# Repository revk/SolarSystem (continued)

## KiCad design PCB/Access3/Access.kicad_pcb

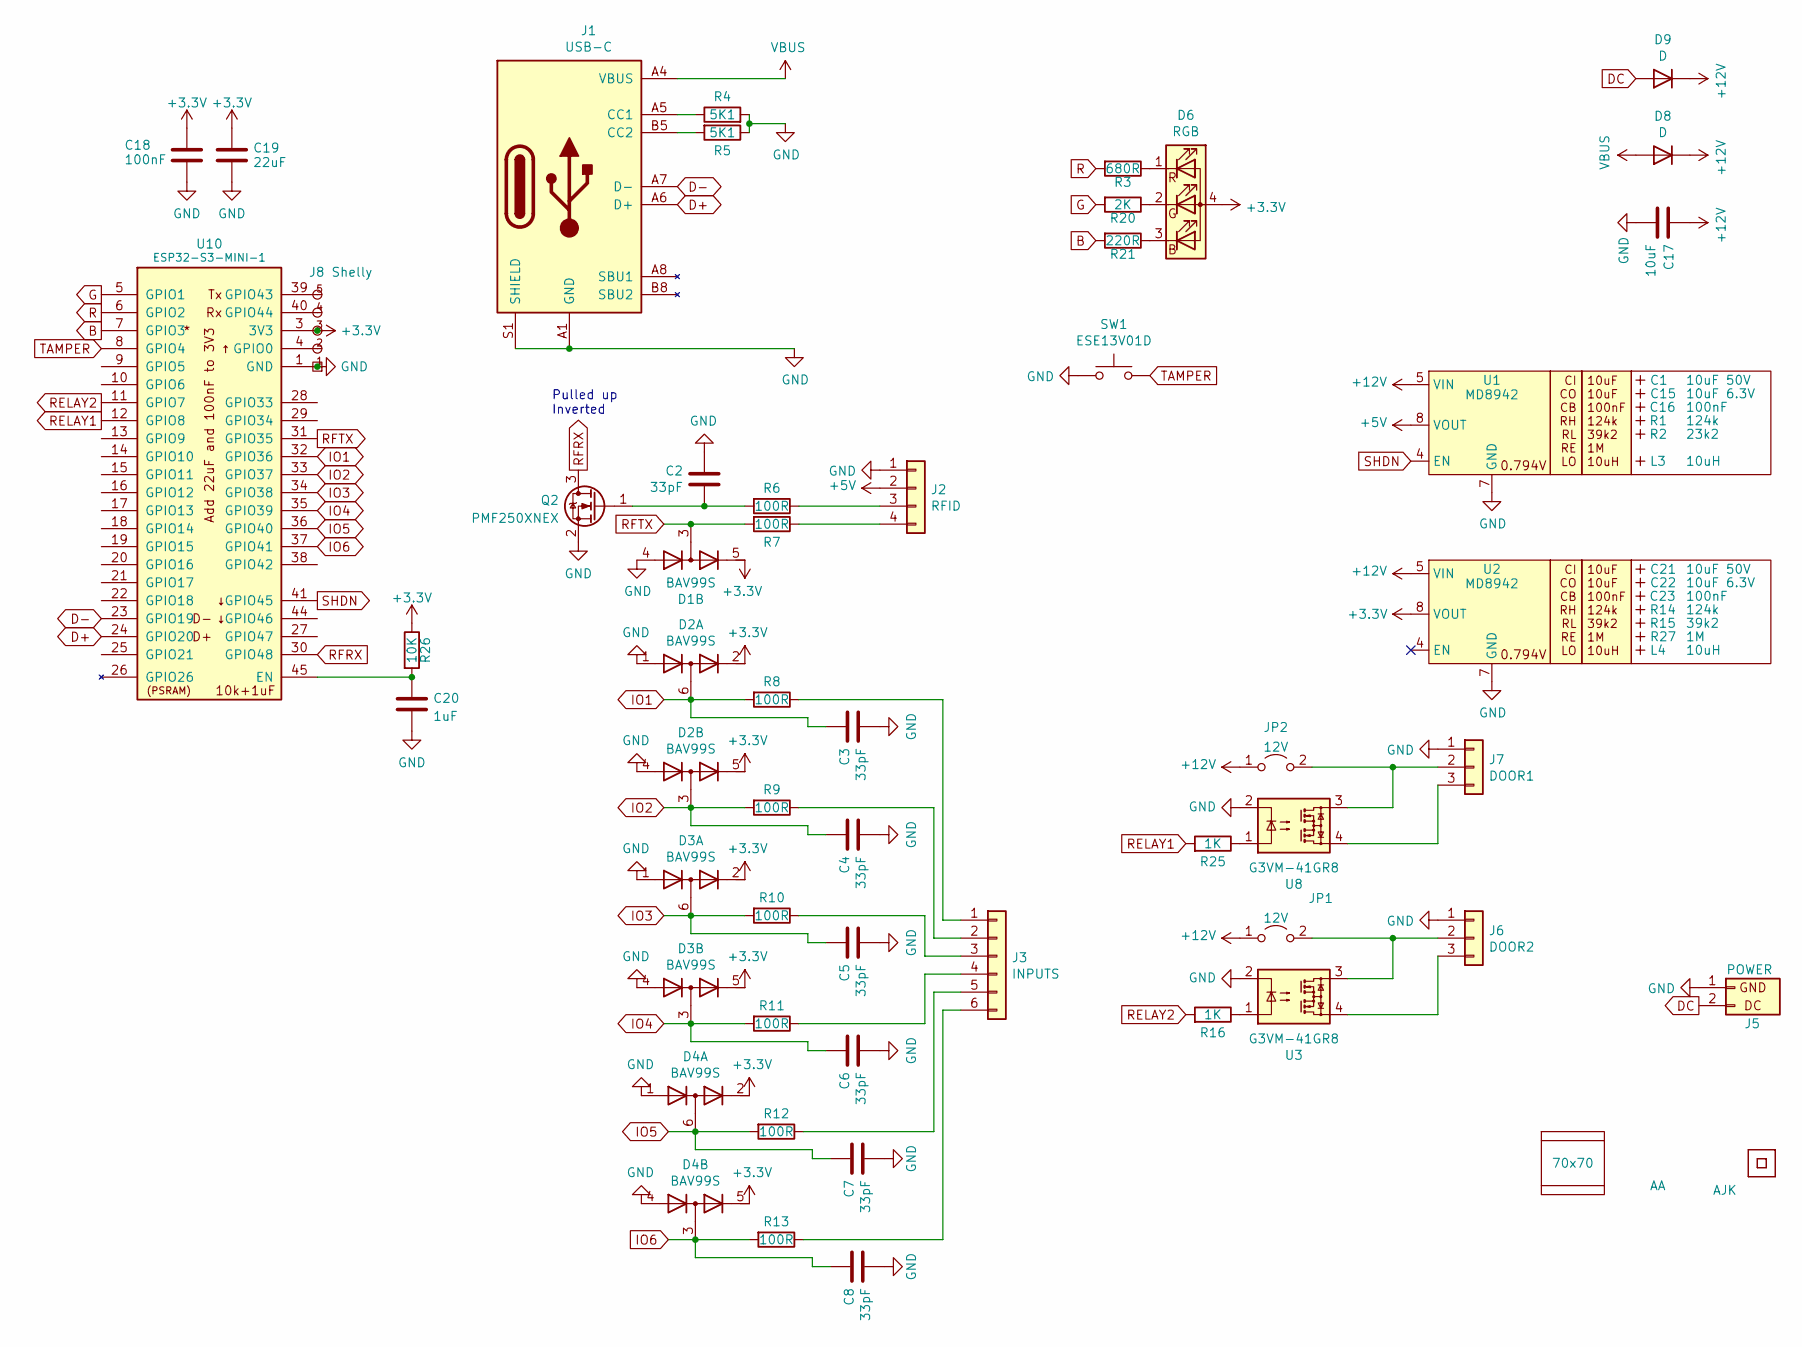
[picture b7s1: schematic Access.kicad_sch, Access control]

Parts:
C1, C21: 10uF 50V; C_0603_; LCSC Part # C1591
C2, C3, C4, C5, C6, C7, C8: 33pF; C_0402
C15, C22: 10uF 6.3V; C_0603_; LCSC Part # C1691
C16, C23: 100nF; C_0603_
C17: 10uF; C_0402
C18: 100nF; C_0402
C19: 22uF; C_0402
C20: 1uF; C_0402
D1, D2, D3, D4: BAV99S; SOT-363_SC-70-6; JLCPCB Rotation Offset 90
D6: RGB; LED-RGB-1.6x1.6; Part No APTF1616LSEEZGKQBKC; LCSC Part # C264508
D8, D9: D; D_1206; LCSC Part # C143805
J1: USB-C; USC16-TR; LCSC Part # C709357
J2: RFID; PTSM-HH-4-RA
J3: INPUTS; PTSM-HH-6-RA
J5: POWER; PTSM-HH1-2-RA
J6: DOOR2; PTSM-HH1-3-RA-W
J7: DOOR1; PTSM-HH1-3-RA
J8: Shelly
JP1, JP2: 12V; SolderJumper-2_P1.3mm_Open_RoundedPad1.0x1.5mm
L3, L4: 10uH; L_4x4_
Logo1: AJK
PCB1: 70x70; PCB7070
Q2: PMF250XNEX; SOT-323_SC-70; Part No PMF250XNEX; LCSC Part # C504047
R1, R14: 124k; R_0402_
R2: 23k2; R_0402_
R3: 680R; R_0402
R4, R5: 5K1; R_0402
R6, R7, R8, R9, R10, R11, R12, R13: 100R; R_0402
R15: 39k2; R_0402_
R16, R25: 1K; R_0402
R20: 2K; R_0402
R21: 220R; R_0402
R26: 10K; R_0402
R27: 1M; R_0402_
SW1: ESE13V01D; ESE13
U1, U2: MD8942; SOT-23-6-MD8942; LCSC Part # C2684786
U3, U8: G3VM-41GR8; Special-SOP-4-3.7x4.55; LCSC Part # C2691601
U7: QR; QR-SS
U9: AA
U10: ESP32-S3-MINI-1; LCSC Part # C3013941
V1, V2: VCUT70

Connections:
+3.3V: C18.1, C19.1, D1.5 (K4), D2.2 (K2), D2.5 (K4), D3.2 (K2), D3.5 (K4), D4.2 (K2), D4.5 (K4), D6.4 (A), J8.3 (3V3), R26.1, U2.8 (VOUT), U10.3 (3V3)
+5V: J2.2, U1.8 (VOUT)
+12V: C17.1, D8.1 (K), D9.1 (K), JP1.1 (A), JP2.1 (A), U1.5 (VIN), U2.5 (VIN)
B: R21.2, U10.7 (GPIO3)
D+: J1.A6 (D+), J1.B6 (D+), U10.24 (GPIO20)
D-: J1.A7 (D-), J1.B7 (D-), U10.23 (GPIO19)
DC: D9.2 (A), J5.2 (DC)
G: R20.2, U10.5 (GPIO1)
GND: C2.1, C3.2, C4.2, C5.2, C6.2, C7.2, C8.2, C17.2, C18.2, C19.2, C20.2, D1.4 (A3), D2.1 (A1), D2.4 (A3), D3.1 (A1), D3.4 (A3), D4.1 (A1), D4.4 (A3), J1.A1 (GND), J1.A12 (GND), J1.B1 (GND), J1.B12 (GND), J1.S1 (SHIELD), J2.1, J5.1 (GND), J6.1, J7.1, J8.1 (GND), Q2.2 (S), R4.2, R5.1, SW1.1, U1.2 (GND), U1.7 (GND), U2.2 (GND), U2.7 (GND), U3.2, U8.2, U10.1 (GND), U10.2 (GND), U10.42 (GND), U10.43 (GND), U10.46 (GND), U10.47 (GND), U10.48 (GND), U10.49 (GND), U10.50 (GND), U10.51 (GND), U10.52 (GND), U10.53 (GND), U10.54 (GND), U10.55 (GND), U10.56 (GND), U10.57 (GND), U10.58 (GND), U10.59 (GND), U10.60 (GND), U10.61 (GND), U10.62 (GND), U10.63 (GND), U10.64 (GND), U10.65 (GND)
IO1: C3.1, D2.6 (K3A4), R8.2, U10.32 (GPIO36)
IO2: C4.1, D2.3 (K1A2), R9.2, U10.33 (GPIO37)
IO3: C5.1, D3.6 (K3A4), R10.2, U10.34 (GPIO38)
IO4: C6.1, D3.3 (K1A2), R11.2, U10.35 (GPIO39)
IO5: C7.1, D4.6 (K3A4), R12.2, U10.36 (GPIO40)
IO6: C8.1, D4.3 (K1A2), R13.2, U10.37 (GPIO41)
unnamed: D6.3 (BK), R21.1
unnamed: D6.2 (GK), R20.1
unnamed: D6.1 (RK), R3.1
unnamed: J1.A5 (CC1), R4.1
unnamed: J1.B5 (CC2), R5.2
unnamed: J2.3, R6.1
unnamed: J2.4, R7.1
unnamed: J3.1, R8.1
unnamed: J3.2, R9.1
unnamed: J3.3, R10.1
unnamed: J3.4, R11.1
unnamed: J3.5, R12.1
unnamed: J3.6, R13.1
unnamed: J6.2, JP1.2 (B), U3.3
unnamed: J6.3, U3.4
unnamed: J7.2, JP2.2 (B), U8.3
unnamed: J7.3, U8.4
unnamed: J8.2 (0), U10.4 (GPIO0)
unnamed: J8.4 (Rx), U10.40 (GPIO44)
unnamed: J8.5 (Tx), U10.39 (GPIO43)
unnamed: C2.2, Q2.1 (G), R6.2
unnamed: R16.1, U3.1
unnamed: R25.1, U8.1
unnamed: C20.1, R26.2, U10.45 (EN)
R: R3.2, U10.6 (GPIO2)
RELAY1: R25.2, U10.12 (GPIO8)
RELAY2: R16.2, U10.11 (GPIO7)
RFRX: Q2.3 (D), U10.30 (GPIO48)
RFTX: D1.3 (K1A2), R7.2, U10.31 (GPIO35)
SHDN: U1.4 (EN), U10.41 (GPIO45)
TAMPER: SW1.2, U10.8 (GPIO4)
VBUS: D8.2 (A), J1.A4 (VBUS), J1.A9 (VBUS), J1.B4 (VBUS), J1.B9 (VBUS)

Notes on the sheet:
Pulled up Inverted

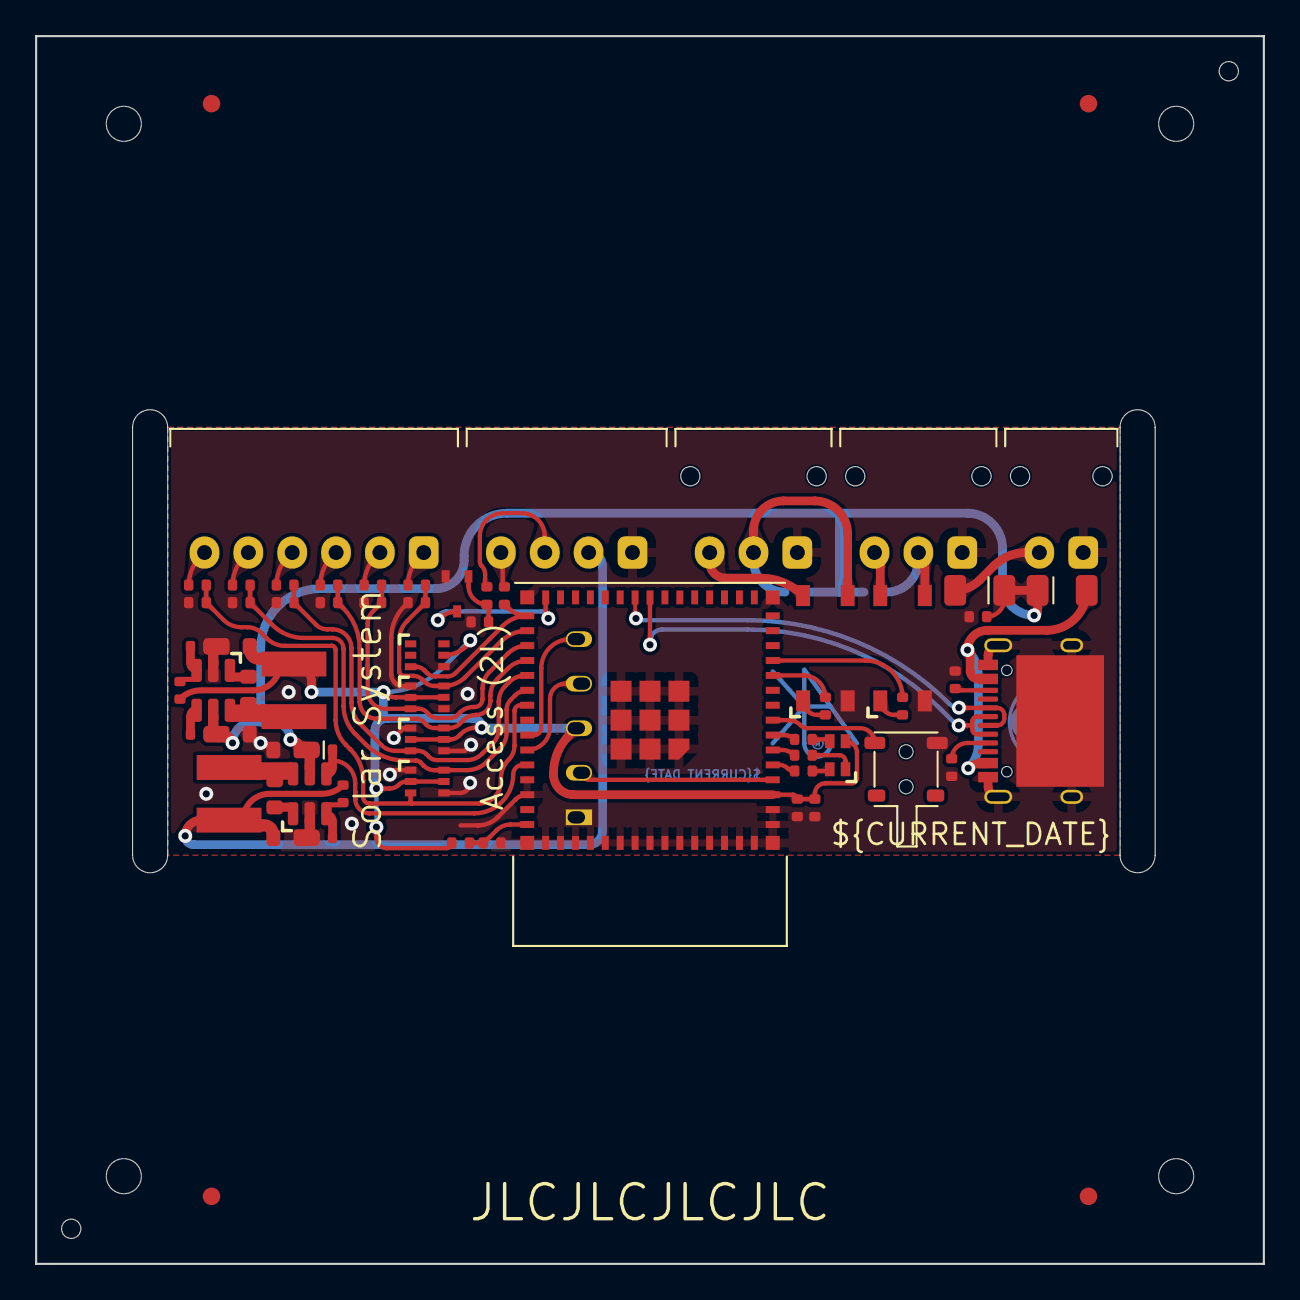
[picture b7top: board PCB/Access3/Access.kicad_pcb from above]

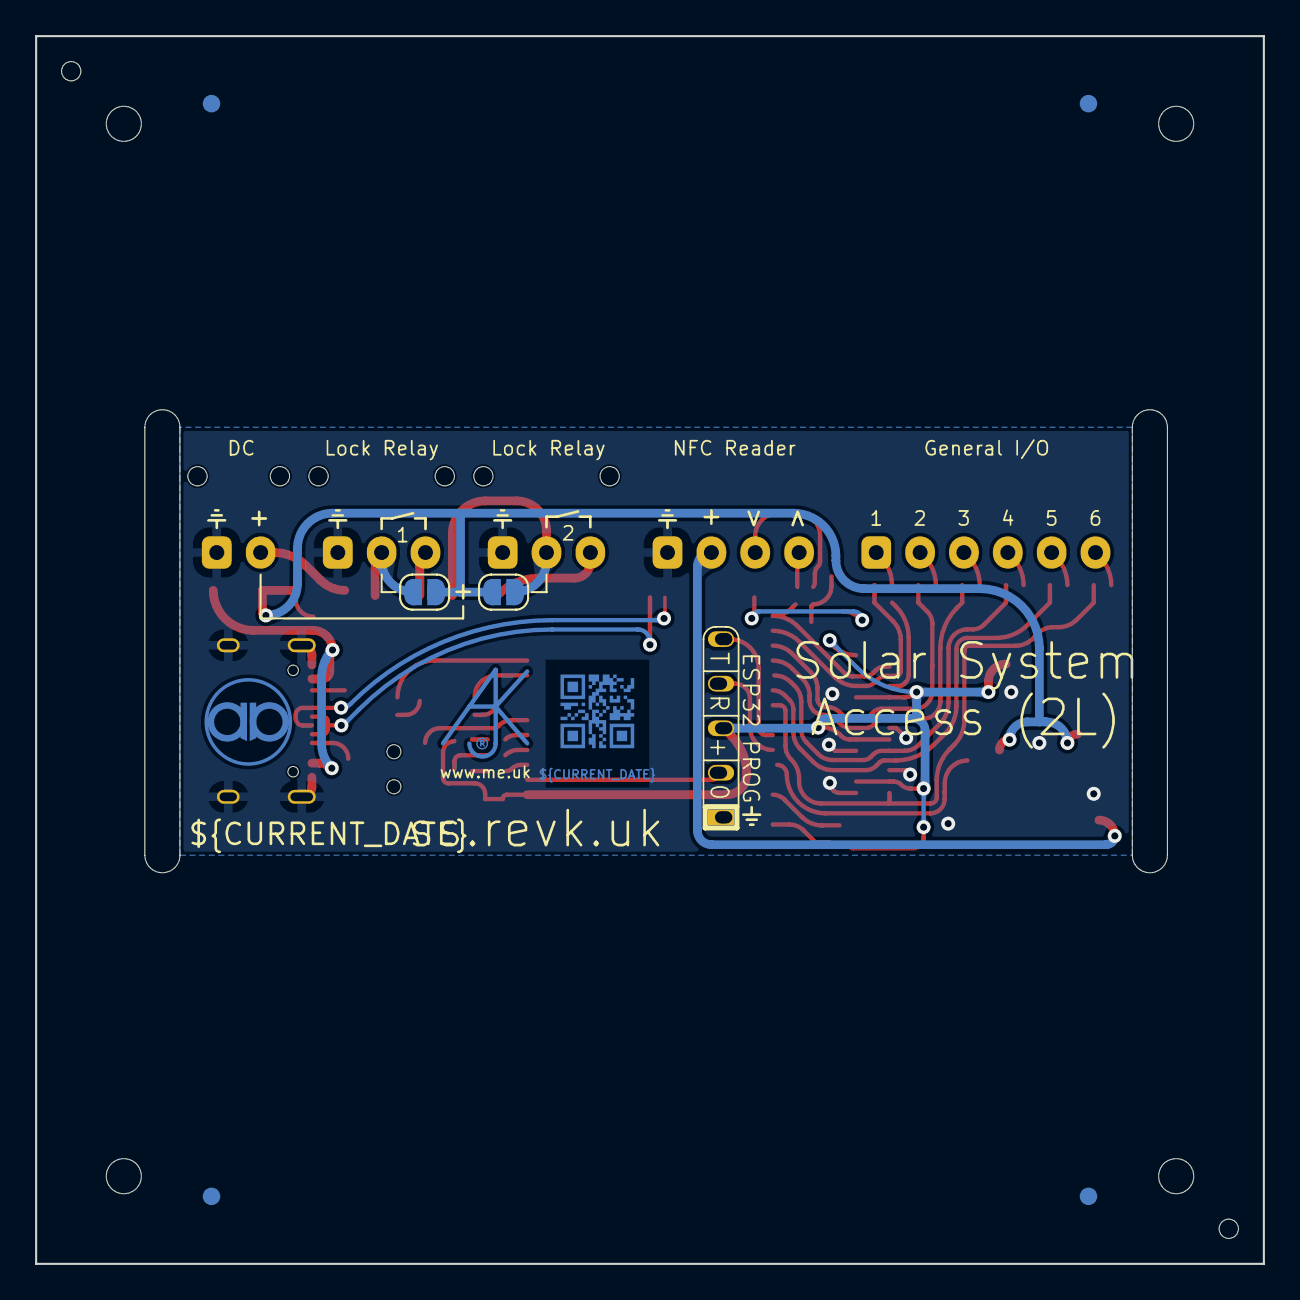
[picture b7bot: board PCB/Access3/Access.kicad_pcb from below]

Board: 2 copper layers, 70.0 x 70.0 mm, 69 parts (6 on the bottom side), 47 nets.

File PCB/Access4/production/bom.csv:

Designator,Footprint,Quantity,Value,LCSC Part #
"C1, C21",C_0603_,2,10uF 50V,C1591
"C15, C22",C_0603_,2,10uF 6.3V,C1691
"C16, C23",C_0603_,2,100nF,
C17,C_0402,1,10uF,
C18,C_0402,1,100nF,
C19,C_0402,1,22uF,
"C2, C3, C4, C5, C6, C7, C8",C_0402,7,33pF,
C20,C_0402,1,1uF,
"D1, D2, D3, D4",SOT-363_SC-70-6,4,BAV99S,
D6,LED-RGB-1.6x1.6,1,RGB,C264508
"D8, D9",D_1206,2,D,C143805
J1,USC16-TR,1,USB-C,C709357
J2,PTSM-HH-4-RA,1,RFID,
J3,PTSM-HH-6-RA,1,INPUTS,
J5,PTSM-HH1-2-RA,1,POWER,
J6,PTSM-HH1-3-RA-W,1,DOOR2,
J7,PTSM-HH1-3-RA,1,DOOR1,
"L3, L4",L_4x4_,2,10uH,
Q2,SOT-323_SC-70,1,PMF250XNEX,C504047
"R1, R14",R_0402_,2,124k,
"R10, R11, R12, R13, R6, R7, R8, R9",R_0402,8,100R,
R15,R_0402_,1,39k2,
"R16, R25",R_0402,2,1K,
R2,R_0402_,1,23k2,
R20,R_0402,1,2K,
R21,R_0402,1,220R,
R26,R_0402,1,10K,
R27,R_0402_,1,1M,
R3,R_0402,1,680R,
"R4, R5",R_0402,2,5K1,
SW1,ESE13,1,ESE13V01D,
"U1, U2",SOT-23-6-MD8942,2,MD8942,C2684786
U10,ESP32-S3-MINI-1,1,ESP32-S3-MINI-1,C3013941
"U3, U8",Special-SOP-4-3.7x4.55,2,G3VM-41GR8,C2691601

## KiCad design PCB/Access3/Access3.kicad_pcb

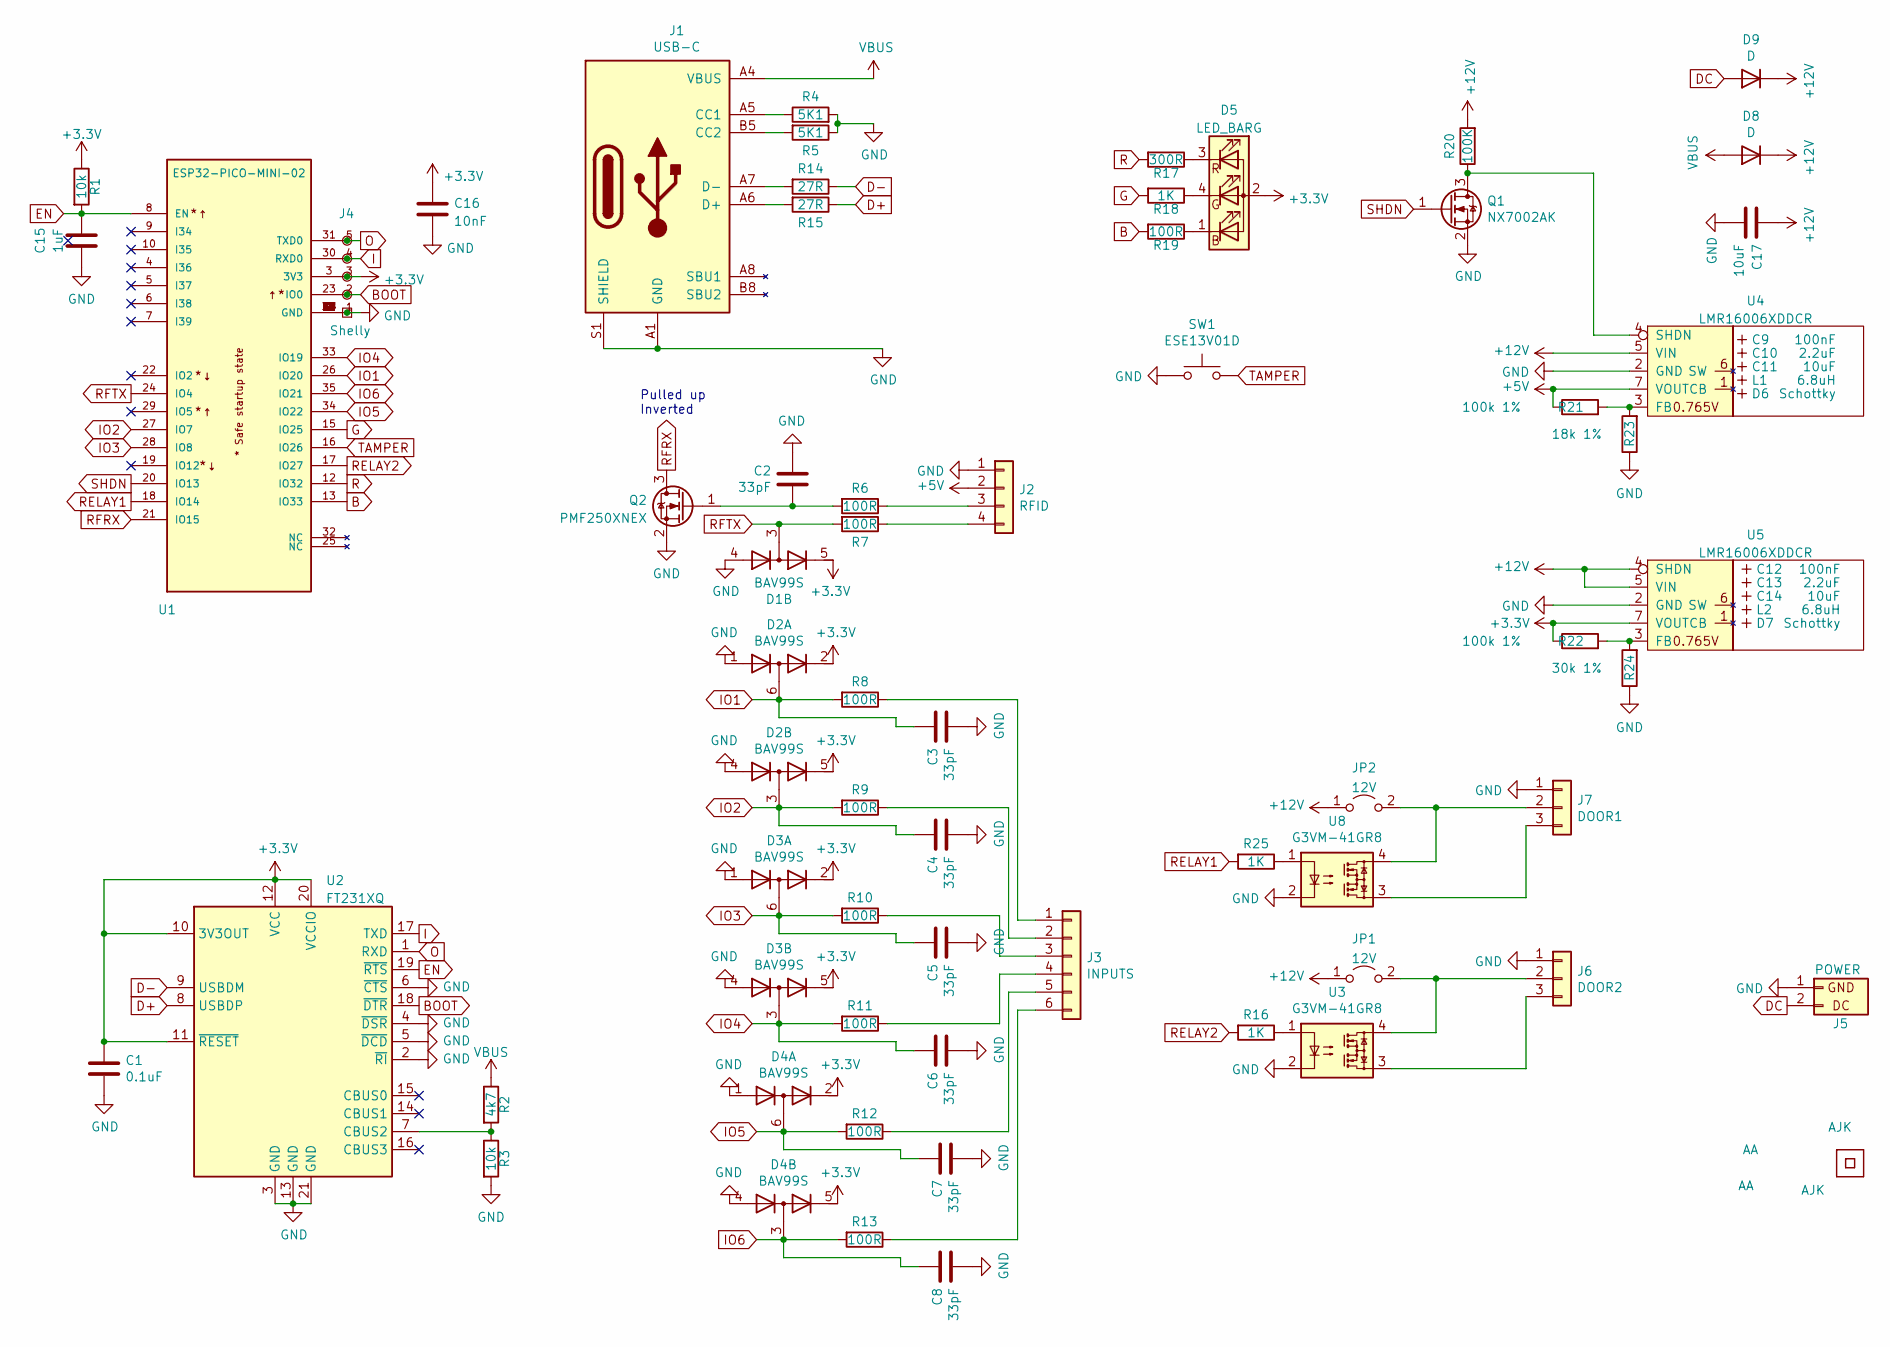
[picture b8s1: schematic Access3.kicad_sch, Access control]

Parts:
AJK1: AJK
C1: 0.1uF; C_0603
C2, C3, C4, C5, C6, C7, C8: 33pF; C_0603
C9, C12: 100nF; C_0603_; LCSC Part # C30926
C10, C13: 2.2uF; C_0805_; LCSC Part # C19110
C11, C14: 10uF; C_0805_; LCSC Part # C17024
C15: 1uF; C_0603
C16: 10nF; C_0603
C17: 10uF; C_0805
D1, D2, D3, D4: BAV99S; SOT-363_SC-70-6; JLCPCB Rotation Offset 90
D5: LED_BARG; MHS190RGBCT; LCSC Part # C409798
D6, D7: Schottky; D_1206_; LCSC Part # C143805
D8, D9: D; D_1206; LCSC Part # C143805
J1: USB-C; USC16-TR; LCSC Part # C709357
J2: RFID; PTSM-HH-4-RA
J3: INPUTS; PTSM-HH-6-RA
J4: Shelly
J5: POWER; PTSM-HH1-2-RA
J6: DOOR2; PTSM-HH1-3-RA-W
J7: DOOR1; PTSM-HH1-3-RA
JP1, JP2: 12V; SolderJumper-2_P1.3mm_Open_RoundedPad1.0x1.5mm
L1, L2: 6.8uH; L_4x4_; LCSC Part # C354575
Logo1: AJK
Q1: NX7002AK; SOT-23; Part No NX7002AK; JLCPCB Rotation Offset 180
Q2: PMF250XNEX; SOT-323_SC-70; Part No PMF250XNEX; LCSC Part # C504047
R1, R3: 10k; R_0603
R2: 4k7; R_0603
R4, R5: 5K1; R_0603
R6, R7, R8, R9, R10, R11, R12, R13: 100R; R_0603
R14, R15: 27R; R_0603
R16, R25: 1K; R_0603
R17: 300R; R_0603; Part No 0603-680R
R18: 1K; R_0603; Part No 0603-2K
R19: 100R; R_0603; Part No 0603-220R
R20: 100K; R_0603
R21, R22: 100k 1%; R_0603; LCSC Part # C14675
R23: 18k 1%; R_0603; LCSC Part # C114610
R24: 30k 1%; R_0603; LCSC Part # C100001
SW1: ESE13V01D; ESE13
U1: ESP32-PICO-MINI-02; PARTREV v1.0; LCSC Part # C2980306
U2: FT231XQ; QFN-20-1EP_4x4mm_P0.5mm_EP2.5x2.5mm; JLCPCB Rotation Offset -90
U3, U8: G3VM-41GR8; Special-SOP-4-3.7x4.55; LCSC Part # C2691601
U4, U5: LMR16006XDDCR; SOT-23-Thin-6-Reg; Part No LMR16006XDDCR; LCSC Part # C87080
U6, U9: AA
U7: QR; QR-SS

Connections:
+3.3V: C1.1, C16.1, D1.5 (K4), D2.2 (K2), D2.5 (K4), D3.2 (K2), D3.5 (K4), D4.2 (K2), D4.5 (K4), D5.2 (A), J4.3 (3V3), R1.1, R22.1, U1.3 (3V3), U2.10 (3V3OUT), U2.11 (~RESET), U2.12 (VCC), U2.20 (VCCIO), U5.7 (VOUT)
+5V: J2.2, R21.1, U4.7 (VOUT)
+12V: C17.1, D8.1 (K), D9.1 (K), JP1.1 (A), JP2.1 (A), R20.2, U4.5 (VIN), U5.4 (SHDN), U5.5 (VIN)
B: R19.2, U1.13 (IO33)
BOOT: J4.2 (0), U1.23 (IO0), U2.18 (~DTR)
D+: R15.1, U2.8 (USBDP)
D-: R14.1, U2.9 (USBDM)
DC: D9.2 (A), J5.2 (DC)
EN: C15.2, R1.2, U1.8 (EN), U2.19 (~RTS)
G: R18.2, U1.15 (IO25)
GND: C1.2, C2.1, C3.2, C4.2, C5.2, C6.2, C7.2, C8.2, C15.1, C16.2, C17.2, D1.4 (A3), D2.1 (A1), D2.4 (A3), D3.1 (A1), D3.4 (A3), D4.1 (A1), D4.4 (A3), J1.A1 (GND), J1.A12 (GND), J1.B1 (GND), J1.B12 (GND), J1.S1 (SHIELD), J2.1, J4.1 (GND), J5.1 (GND), J6.1, J7.1, Q1.2 (S), Q2.2 (S), R3.2, R4.2, R5.1, R23.1, R24.1, SW1.1, U1.1 (GND), U1.2 (GND), U1.11 (GND), U1.14 (GND), U1.36 (GND), U1.37 (GND), U1.38 (GND), U1.39 (GND), U1.40 (GND), U1.41 (GND), U1.42 (GND), U1.43 (GND), U1.44 (GND), U1.45 (GND), U1.46 (GND), U1.47 (GND), U1.48 (GND), U1.49 (GND), U1.50 (GND), U1.51 (GND), U1.52 (GND), U1.53 (GND), U2.2 (~RI), U2.3 (GND), U2.4 (~DSR), U2.5 (~DCD), U2.6 (~CTS), U2.13 (GND), U2.21 (GND), U3.2, U4.2 (GND), U5.2 (GND), U8.2
I: J4.4 (Rx), U1.30 (RXD0), U2.17 (TXD)
IO1: C3.1, D2.6 (K3A4), R8.2, U1.26 (IO20)
IO2: C4.1, D2.3 (K1A2), R9.2, U1.27 (IO7)
IO3: C5.1, D3.6 (K3A4), R10.2, U1.28 (IO8)
IO4: C6.1, D3.3 (K1A2), R11.2, U1.33 (IO19)
IO5: C7.1, D4.6 (K3A4), R12.2, U1.34 (IO22)
IO6: C8.1, D4.3 (K1A2), R13.2, U1.35 (IO21)
unnamed: D5.1 (BK), R19.1
unnamed: D5.4 (GK), R18.1
unnamed: D5.3 (RK), R17.1
unnamed: J1.A5 (CC1), R4.1
unnamed: J1.B5 (CC2), R5.2
unnamed: J1.A6 (D+), J1.B6 (D+), R15.2
unnamed: J1.A7 (D-), J1.B7 (D-), R14.2
unnamed: J2.3, R6.1
unnamed: J2.4, R7.1
unnamed: J3.1, R8.1
unnamed: J3.2, R9.1
unnamed: J3.3, R10.1
unnamed: J3.4, R11.1
unnamed: J3.5, R12.1
unnamed: J3.6, R13.1
unnamed: J6.2, JP1.2 (B), U3.4
unnamed: J6.3, U3.3
unnamed: J7.2, JP2.2 (B), U8.4
unnamed: J7.3, U8.3
unnamed: Q1.3 (D), R20.1, U4.4 (SHDN)
unnamed: C2.2, Q2.1 (G), R6.2
unnamed: R16.1, U3.1
unnamed: R25.1, U8.1
unnamed: R2.2, R3.1, U2.7 (CBUS2)
unnamed: R21.2, R23.2, U4.3 (FB)
unnamed: R22.2, R24.2, U5.3 (FB)
O: J4.5 (Tx), U1.31 (TXD0), U2.1 (RXD)
R: R17.2, U1.12 (IO32)
RELAY1: R25.2, U1.18 (IO14)
RELAY2: R16.2, U1.17 (IO27)
RFRX: Q2.3 (D), U1.21 (IO15)
RFTX: D1.3 (K1A2), R7.2, U1.24 (IO4)
SHDN: Q1.1 (G), U1.20 (IO13)
TAMPER: SW1.2, U1.16 (IO26)
VBUS: D8.2 (A), J1.A4 (VBUS), J1.A9 (VBUS), J1.B4 (VBUS), J1.B9 (VBUS), R2.1

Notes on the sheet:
Pulled up Inverted

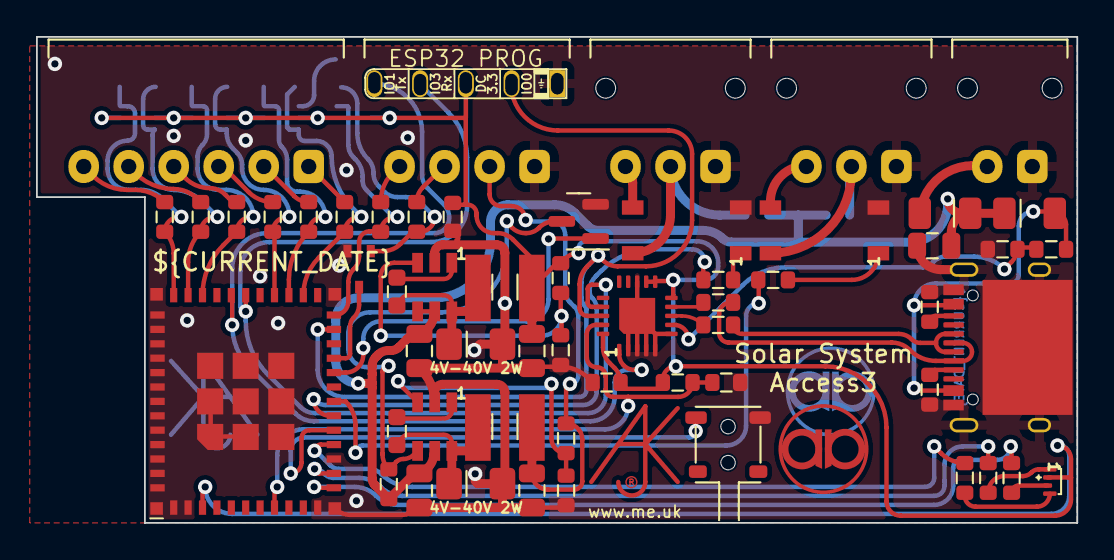
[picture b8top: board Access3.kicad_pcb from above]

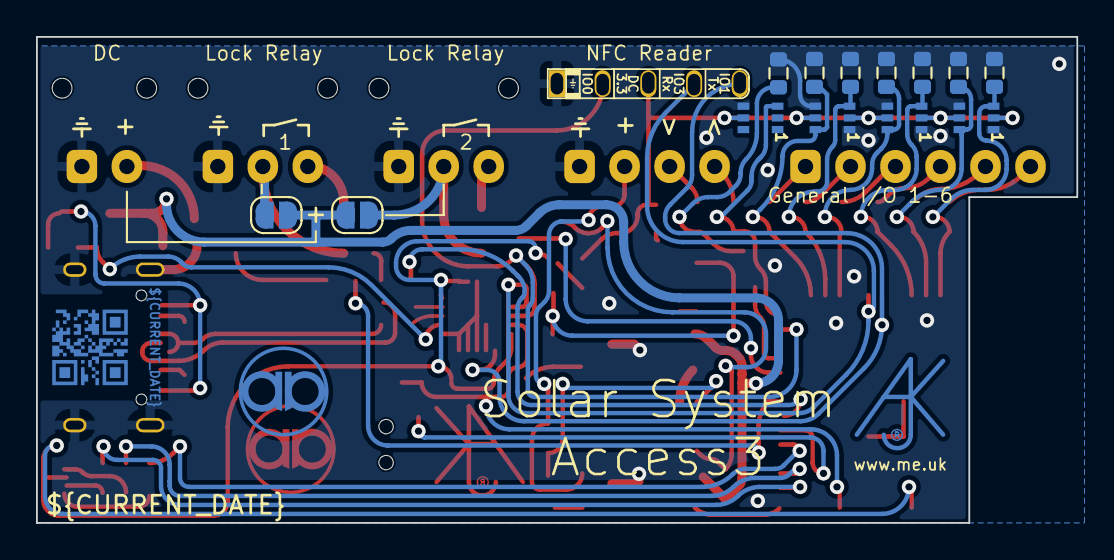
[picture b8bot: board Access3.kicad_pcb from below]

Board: 2 copper layers, 57.8 x 27.0 mm, 76 parts (16 on the bottom side), 53 nets.

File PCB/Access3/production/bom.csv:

Designator,Footprint,Quantity,Value,LCSC Part #
C1,C_0603,1,0.1uF,
"C10, C13",C_0805_,2,2.2uF,C19110
"C11, C14",C_0805_,2,10uF,C17024
"C12, C9",C_0603_,2,100nF,C30926
"C15, C16",C_0603,2,10nF,
C17,C_0805,1,10uF,
"C2, C3, C4, C5, C6, C7, C8",C_0603,7,33pF,
"D1, D2, D3, D4",SOT-363_SC-70-6,4,BAV99S,
D5,MHS190RGBCT,1,LED_BARG,C409798
"D6, D7",D_1206_,2,Schottky,C143805
"D8, D9",D_1206,2,D,C143805
J1,USC16-TR,1,USB-C,C709357
J2,PTSM-HH-4-RA,1,RFID,
J3,PTSM-HH-6-RA,1,INPUTS,
J5,PTSM-HH1-2-RA,1,POWER,
J6,PTSM-HH1-3-RA-W,1,DOOR2,
J7,PTSM-HH1-3-RA,1,DOOR1,
"L1, L2",L_4x4_,2,6.8uH,C354575
Q1,SOT-23,1,NX7002AK,
Q2,SOT-323_SC-70,1,PMF250XNEX,C504047
"R1, R3",R_0603,2,10k,
"R10, R11, R12, R13, R19, R6, R7, R8, R9",R_0603,9,100R,
"R14, R15",R_0603,2,27R,
"R16, R18, R25",R_0603,3,1K,
R17,R_0603,1,300R,
R2,R_0603,1,4k7,
R20,R_0603,1,100K,
"R21, R22",R_0603,2,100k 1%,C14675
R23,R_0603,1,18k 1%,C114610
R24,R_0603,1,30k 1%,C100001
"R4, R5",R_0603,2,5K1,
SW1,ESE13,1,ESE13V01D,
U1,ESP32-PICO-MINI-02,1,ESP32-PICO-MINI-02,C2980306
U2,QFN-20-1EP_4x4mm_P0.5mm_EP2.5x2.5mm,1,FT231XQ,
"U3, U8",Special-SOP-4-3.7x4.55,2,G3VM-41GR8,C2691601
"U4, U5",SOT-23-Thin-6-Reg,2,LMR16006XDDCR,C87080

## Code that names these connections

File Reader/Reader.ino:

// RFID Card reader for Solar System
// ESP-12F based for use with MFRC522 to send on card read

// Witing for ESP-12F
// RC522 connnections (in addition to GND/3V3)
// GPIO2  RST (not actually needed)
// GPIO13 MOSI
// GPIO12 MISO
// GPIO14 SCK (CLK)
// GPIO16 SDA (SS)

// TODO
// HoldTime as a setting
// More checks on MiFare card validity (key as a setting)

#define HOLDTIME 3000
#define RELEASETIME 1000

#include <ESP8266RevK.h>

ESP8266RevK revk(__FILE__, __DATE__ " " __TIME__);

#define RST 2 // SPI
#define SS 16 // SPI

#include <SPI.h>
#include <MFRC522.h>
MFRC522 rfid(SS, RST); // Instance of the class

boolean app_setting(const char *setting, const byte *value, size_t len)
{ // Called for settings retrieved from EEPROM
  return false; // Done
}

boolean app_cmnd(const char*suffix, const byte *message, size_t len)
{ // Called for incoming MQTT messages
  return false;
}

void setup()
{
  SPI.begin(); // Init SPI bus
  rfid.PCD_Init(); // Init MFRC522
}

void loop()
{
  revk.loop();
  long now = (millis() ? : 1); // Allowing for wrap, and using 0 to mean not set
  static long cardcheck = 0;
  if ((int)(cardcheck - now) < 0)
  {
    cardcheck = now + 100;
    static byte id[4] = {};
    static long first = 0;
    static long last = 0;
    static boolean held = false;
    if (rfid.PICC_IsNewCardPresent() && rfid.PICC_ReadCardSerial())
    {
      last = now;
      MFRC522::PICC_Type piccType = rfid.PICC_GetType(rfid.uid.sak);
      if (!first || memcmp(id, rfid.uid.uidByte, 4))
      {
        if (held)
          revk.stat("gone", "%02X%02X%02X%02X", id[0], id[1], id[2], id[3]); // Edge case of change card after hold before release time
        first = now;
        held = false;
        memcpy(id, rfid.uid.uidByte, 4);
        revk.stat("id", "%02X%02X%02X%02X", id[0], id[1], id[2], id[3]);
      } else if (!held && first && (int)(now - first) > HOLDTIME)
      {
        held = true;
        revk.stat( "held", "%02X%02X%02X%02X", id[0], id[1], id[2], id[3]);
      }
    } else if (last && (int)(now - last) > RELEASETIME)
    {
      if (held)
        revk.stat("gone", "%02X%02X%02X%02X", id[0], id[1], id[2], id[3]);
      first = 0;
      last = 0;
      held = false;
    }
  }
}

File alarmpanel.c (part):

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}

#define	port_exit_set(g,w,v,p,door,d) port_exit_set_n(port_set_n(g,(volatile port_p*)&(w),sizeof(w)/sizeof(port_p),v,p,1,door,"Exit"),sizeof(w)/sizeof(port_p),d)
#define	port_bell_set(g,w,v,p,door) port_bell_set_n(port_set_n(g,(volatile port_p*)&(w),sizeof(w)/sizeof(port_p),v,p,1,door,"Bell"),sizeof(w)/sizeof(port_p))
#define	port_i_set(g,w,v,p,door,name) port_set_n(g,(volatile port_p*)&(w),sizeof(w)/sizeof(port_p),v,p,1,door,name)
#define	port_o_set(g,w,v,p,door,name) port_set_n(g,(volatile port_p*)&(w),sizeof(w)/sizeof(port_p),v,p,0,door,name)
#define	port_set(g,w,v,p,door,name) port_set_n(g,(volatile port_p*)&(w),sizeof(w)/sizeof(port_p),v,p,-1,door,name)
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            if ((v = xml_get(x, "@quiet")) && !strcasecmp(v, "true"))
               k->k.quiet = 1;
            if (!(v = xml_get(x, "@dark")) || strcasecmp(v, "true"))
               k->k.backlight = 1;
            port_app(p)->group |= k->groups;
         }
   }
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         {
            if (!d->tamper)
            {
               d->tamper = 1;
               add_tamper(d->group_lock, doorno, doorname, e->message);
            }
         } else
         {
            if (d->tamper)
            {
               d->tamper = 0;
               rem_tamper(d->group_lock, doorno, doorname, e->message);
            }
         }
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         {
            if (!app->tamper)
            {
               app->tamper = 1;
               if (walkthrough)
                  syslog(LOG_INFO, "+%s(%s) Tamper %s", tag, name ? : "", e->message ? : "");
               add_tamper(g, tag, name, e->message);
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         {
            if (app->tamper)
            {
               app->tamper = 0;
               if (walkthrough)
                  syslog(LOG_INFO, "-%s(%s) Tamper %s", tag, name ? : "", e->message ? : "");
               rem_tamper(g, tag, name, e->message);
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
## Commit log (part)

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2023-12-22 Library update
2023-12-22 More work on 3D
2023-12-25 Tidy
2023-12-27 Updated 3D
2023-12-27 Silly mistake in LED config
2023-12-27 Order
2023-12-27 order and layout
2023-12-27 Tidy LED
2023-12-28 debug
2023-12-28 LEDs
2023-12-28 Reverse polarty
2023-12-28 Brackets
2023-12-28 Tidy 3D
2024-01-01 Moved to GPS project
2024-01-02 Clear to avoid solder draining down hole instead of pad
2024-01-05 Fix GPIO 40 limit
2024-01-05 Provision with device copy
2024-01-05 Silly
2024-01-05 Silly bug
2024-01-05 Catch duplicates
2024-01-18 Baud change
2024-01-19 Add actual config FFS
2024-01-19 Default baud rate fix
2024-01-23 More stack
2024-01-23 No LED strip on V1
2024-01-23 Revert led_strip change
2024-01-23 Cleaner
2024-01-26 nfcbaud
2024-01-26 Change of prefix
2024-01-26 Allow SS:
2024-02-09 New library (old settings)
2024-02-10 New settings system in RevK library
2024-02-10 New settings
2024-02-10 Fixed PCb editr
2024-02-10 isXXX
2024-02-11 Try cleaner shutdown
2024-02-11 Tweak for testing
2024-02-11 Tytpo
2024-02-11 Split brain detect and reset
2024-02-11 shutdown message
2024-02-11 Check
2024-02-11 Message
2024-02-13 Revise poke logic
2024-02-13 Revised poke
2024-02-13 FFS that is why it reboots, ejit
2024-02-13 New default
2024-02-21 Handle raw strings
2024-03-04 Tidy up PCb
2024-03-15 Tidy PCB
2024-03-15 origin
2024-03-16 New revk_restart()
2024-03-16 Year
2024-03-21 Colour wrong on inputs
2024-03-21 FFS live engineer change
2024-03-21 Tweak order
2024-05-12 5.2.1 and library update
2024-05-12 PN532 TX Buf fix
2024-05-12 Try that
2024-05-12 Change timeout
2024-05-12 Latest mesh tweaks
2024-05-12 Remove TOS as INVALID ARGUMENT error?!
2024-05-12 More testing
2024-05-12 try this
2024-05-12 Better log
2024-05-12 Typo
2024-05-13 Timeout
2024-08-03 Updated library and updated galaxybus
2024-08-03 Don't auto update even root node
2024-08-04 Library
2024-08-04 Library (logging updates)
2024-08-04 Library (logging)
2024-08-04 Boot time
2024-08-04 Hmmm
2024-08-04 New uptime field
2024-08-04 Keep alive checks
2024-08-04 Librray
2024-08-04 Tryu that
2024-08-04 Cleaner sub/unsub
2024-08-04 Try new features
2024-08-04 802.11r
2024-08-04 trying to fix bufffers
2024-08-05 Faster wifi
2024-08-05 Subscribe fix
2024-08-05 Comments
2024-08-16 Cannot make production files, FFS
2024-08-30 Fix update
2024-09-24 New PIN handling logic
2024-09-24 New lib
2024-09-24 Strong PIN arm
2024-09-24 Cleaner errors
2024-09-25 New keypad.pinarm setting
2024-09-25 SSL compat
2024-09-25 Fix keystrong
2024-12-12 New PCB design using WAGOs
2024-12-16 Silkscreen, and 21
2024-12-31 Trying to sort led strip
2024-12-31 IPv6
2024-12-31 Not dhpcv6
2025-01-04 Fix host
2025-01-13 New images
2025-01-13 Settings
2025-01-13 Tweak
2025-01-13 Render
2025-01-19 Images
2025-01-19 More images
2025-01-19 Images and cleanup
2025-01-19 Latest WAGO boards
2025-01-23 PCB Update
2025-03-26 Component fix
2025-04-18 Bell WAGO and other updates and renders
2025-07-30 Latest library
2025-07-30 Expoental PIN backoff
2025-08-09 Case update
2025-08-12 new render and case
2025-08-13 New case
2025-08-18 WAGO pins
2025-08-28 Added idle led timeout on NFC reader
2025-09-18 Avoid disarm/hold/arm scenario
2025-09-18 Disarm beep
2025-09-20 Fix disarm message, and more distinctive beep
2025-09-20 Tweak beeps
2025-09-20 Fix disarm logic
2025-09-20 Cleaner arm/disarm message and beep logic
2025-09-20 Upgrade display message
2025-10-09 New LEDs
2025-10-17 Blocked
